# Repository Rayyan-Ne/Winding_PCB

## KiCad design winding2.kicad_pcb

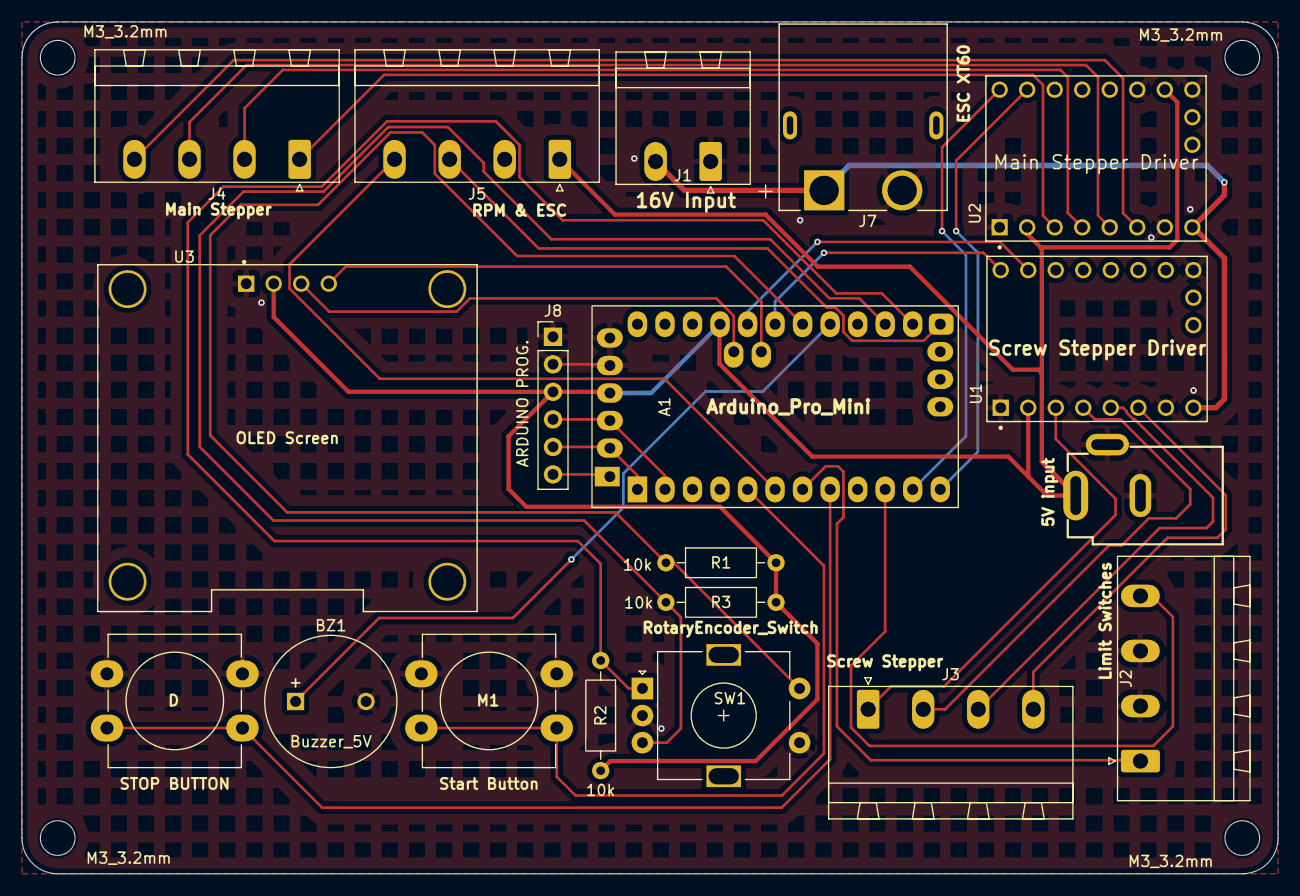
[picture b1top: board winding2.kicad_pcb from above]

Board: 2 copper layers, 115.9 x 78.6 mm, 23 parts (0 on the bottom side), 30 nets.

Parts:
A1: Arduino_Pro_Mini; Arduino_Pro_Mini(with_programming_pins)
BZ1: Buzzer_5V; MagneticBuzzer_ProSignal_ABT-410-RC
J1: Screw_Terminal_2_P5.00mm; PhoenixContact_MSTBA_2,5_2-G-5,08_1x02_P5.08mm_Horizontal
J2: Limit Switches; PhoenixContact_MSTBA_2,5_4-G-5,08_1x04_P5.08mm_Horizontal
J3: Screw Stepper; PhoenixContact_MSTBA_2,5_4-G-5,08_1x04_P5.08mm_Horizontal
J4: Main Stepper; PhoenixContact_MSTBA_2,5_4-G-5,08_1x04_P5.08mm_Horizontal
J5: RPM & ESC; PhoenixContact_MSTBA_2,5_4-G-5,08_1x04_P5.08mm_Horizontal
J6: 5V input; Barrel_Jack_PTH_Slot
J7: ESC XT60; AMASS_XT60PW-F
J8: ARDUINO PROG.; PinHeader_1x06_P2.54mm_Vertical
M3_3.2mm, M3_3.2mm#2, M3_3.2mm#3, M3_3.2mm#4: MountingHole_3.2mm_M3_DIN965
R1, R2, R3: 10k; R_Axial_DIN0207_L6.3mm_D2.5mm_P10.16mm_Horizontal
STOP BUTTON: Push_Button_W12mm
SW1: RotaryEncoder_Switch; RotaryEncoder_Alps_EC11E-Switch_Vertical_H20mm
Start Button: Push_Button_W12mm
U1, U2: TMC2209_SILENTSTEPSTICK; MODULE_TMC2209_SILENTSTEPSTICK
U3: OLED Screen; MODULE_DM-OLED096-636

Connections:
5V: A1.24 (VCC), A1.30 (VCC), J5.1, J6.PWR, J8.3, R1.2, R2.2, R3.2, U1.2 (VIO), U2.2 (VIO), U2.15 (MS1), U3.2 (VCC_IN)
+16V: J1.2, J7.1, U1.8 (VM), U2.8 (VM)
/Ard_Rx: A1.2 (0/RX), J8.4
/Ard_Tx: A1.1 (1/TX), J8.5
/BUZZ-A0: A1.20 (A0), BZ1.1
/DIR1: A1.11 (8), U2.9 (DIR)
/DIR2: A1.22 (A2), U1.9 (DIR)
/DTR: A1.31 (DTR), J8.6
/D_Button: A1.8 (5/PWM), STOP BUTTON.1
/ENCODER_A: A1.17 (11/PWM), R2.1, SW1.A
/ENCODER_B: A1.18 (12), R3.1, SW1.B
/ENCODER_SW: A1.21 (A1), R1.1, SW1.S2
/ESC-S: A1.16 (10/PWM), J5.3
/M1A: J4.2, U2.4 (M1A)
/M1B: J4.1, U2.3 (M1B)
/M1_Button: A1.5 (2), Start Button.1
/M2A: J4.3, U2.5 (M2A)
/M2B: J4.4, U2.6 (M2B)
/OLED-A4: A1.33 (SDA/A4), U3.4 (SDA)
/OLED-A5: A1.32 (SCL/A5), U3.3 (SCL)
/RPM: A1.6 (3/PWM), J5.4
/S1A: J3.2, U1.4 (M1A)
/S1B: J3.1, U1.3 (M1B)
/S2A: J3.3, U1.5 (M2A)
/S2B: J3.4, U1.6 (M2B)
/STP1: A1.12 (9/PWM), U2.10 (STEP)
/STP2: A1.23 (A3), U1.10 (STEP)
/limit1: A1.7 (4), J2.1
/limit2: A1.10 (7), J2.4
GND: A1.28 (GND), A1.29 (GND), BZ1.2, J1.1, J2.2, J2.3, J5.2, J6.GND, J6.GNDBREAK, J7.2 (N), J8.1, J8.2, STOP BUTTON.2, SW1.C, SW1.S1, Start Button.2, U1.1 (GND), U1.7 (GND), U1.16 (~EN), U2.1 (GND), U2.7 (GND), U2.14 (MS2), U2.16 (~EN), U3.1 (GND)

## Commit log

2026-01-16 first commit - initial scratching files
2026-01-16 gitignore file edited
2026-01-17 Adding the second TMC2209 stepper driver and wiring both drivers
2026-01-17 updating the PCB file - still ongoing
2026-01-21 finalize the schematic part and footprints assigning step
2026-01-21 editing the OLED screen footprint
2026-01-21 initial placing and layout of components
2026-01-21 fix: adding missing stepper motors connections and PWR_FLAG labels
2026-01-22 trial: testing the free router plugin
2026-01-23 Manual routing with ground plan - v0.0
2026-01-23 releases folder added with v0.0 greber files
2026-01-23 version added to sch and pcb sheets
2026-01-29 rearranging components to be more user freindly and added front GND Zone
2026-01-29 mounting holes added and errors fixed
2026-01-29 GND zones modified and board dimensions updated
2026-01-31 mounting holes dimensions changed to M3 and edge cuts layer changed to curved one
2026-01-31 mounting holes silkscreen label added
2026-01-31 kıcad metadata mınor changes
